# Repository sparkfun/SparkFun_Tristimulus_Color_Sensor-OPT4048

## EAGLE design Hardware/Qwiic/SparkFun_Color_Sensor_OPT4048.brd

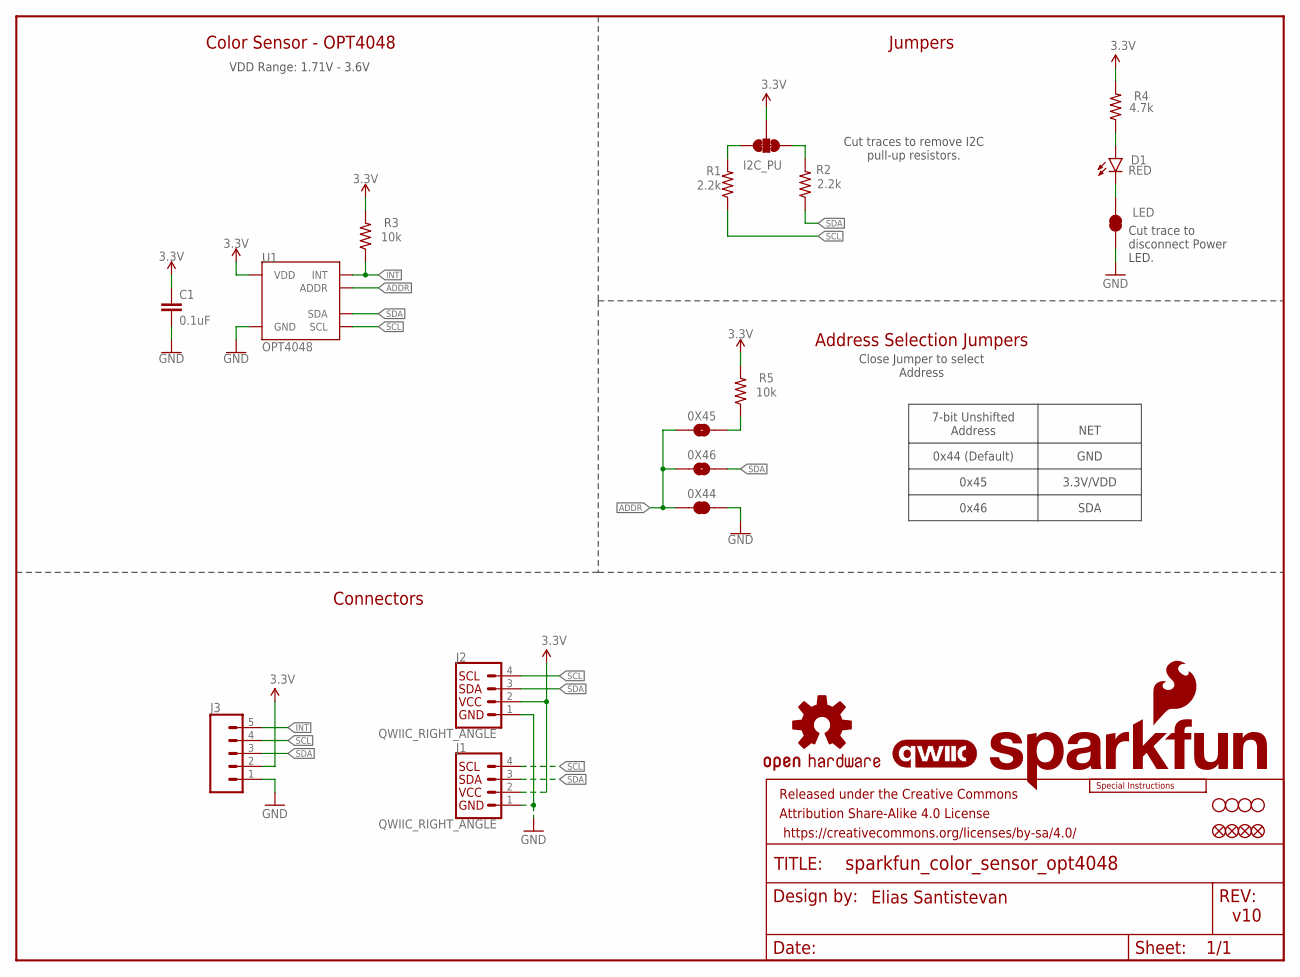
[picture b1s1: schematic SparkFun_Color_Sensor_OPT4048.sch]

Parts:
0X44: JUMPER-SMT_2_NC_TRACE_SILK; SMT-JUMPER_2_NC_TRACE_SILK
0X45, 0X46: JUMPER-SMT_2_NO_SILK; SMT-JUMPER_2_NO_SILK
C1: 0.1uF; 0402-TIGHT
D1: RED; LED-0603
FD1, FD2: FIDUCIALUFIDUCIAL; FIDUCIAL-MICRO
FID1, FID2: FIDUCIALUFIDUCIAL; FIDUCIAL-MICRO
FRAME1: FRAME-LETTER; CREATIVE_COMMONS
I2C_PU: S_MODE; SMT-JUMPER_3_2-NC_TRACE_SILK
J1, J2: QWIIC_RIGHT_ANGLE; JST04_1MM_RA
J3: CONN_05NO_SILK; 1X05_NO_SILK
LED: JUMPER-SMT_2_NC_TRACE_SILK; SMT-JUMPER_2_NC_TRACE_SILK
LOGO1: QWIIC_LOGO_4MM; QWIIC_4MM
LOGO2: OSHW-LOGOMINI; OSHW-LOGO-MINI
LOGO3: SFE_LOGO_NAME_FLAME.1_INCH; SFE_LOGO_NAME_FLAME_.1
LOGO4: SPECIAL_INSTRUCTIONS-ORDERING; ORDERING_INSTRUCTIONS
R1, R2: 2.2k; 0603
R3, R5: 10k; 0603
R4: 4.7k; 0603
STANDOFF1, STANDOFF2, STANDOFF3, STANDOFF4: STAND-OFFTIGHT; STAND-OFF-TIGHT
U1: OPT4048; FCSOT

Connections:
3.3V: C1.1, I2C_PU.2, J1.2, J2.2, J3.2, R3.2, R4.2, R5.2, U1.P1 (VDD)
ADDR: 0X44.1, 0X45.1, 0X46.1, U1.P2 (ADDR)
GND: 0X44.2, C1.2, J1.1, J2.1, J3.1, LED.1, U1.P4 (GND)
INT: J3.5, R3.1, U1.P7 (INT)
unnamed: D1.A, R4.1
unnamed: D1.C, LED.2
unnamed: 0X45.2, R5.1
unnamed: I2C_PU.1, R1.2
unnamed: I2C_PU.3, R2.2
SCL: J1.4, J2.4, J3.4, R1.1, U1.P5 (SCL)
SDA: 0X46.2, J1.3, J2.3, J3.3, R2.1, U1.P8 (SDA)

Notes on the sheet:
Color Sensor - OPT4048
Cut traces to remove I2C pull-up resistors.
VDD Range: 1.71V - 3.6V
v10
Jumpers
Cut trace to disconnect Power LED.
Connectors
Elias Santistevan
7-bit Unshifted Address
0x44 (Default)
0x45
0x46
GND
3.3V/VDD
SDA
Address Selection Jumpers
NET
Close Jumper to select Address

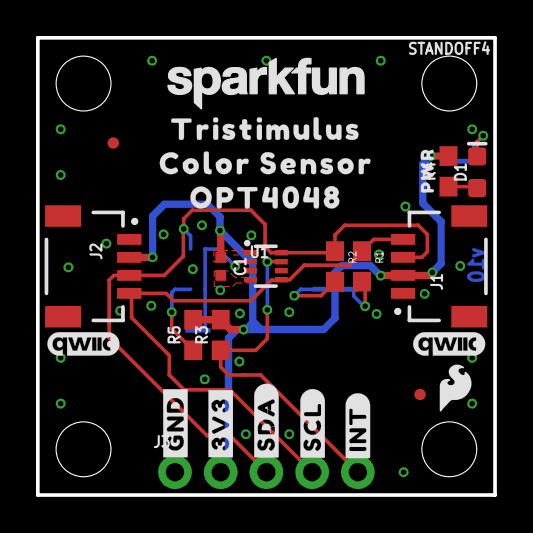
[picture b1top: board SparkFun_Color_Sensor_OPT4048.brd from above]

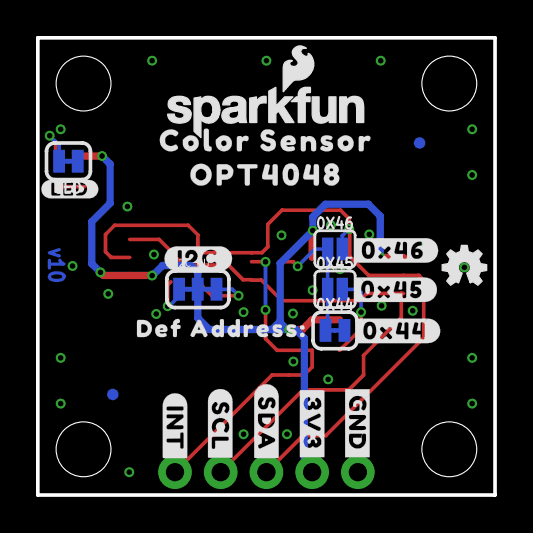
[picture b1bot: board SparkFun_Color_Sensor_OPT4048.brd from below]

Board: 2 copper layers, 25.4 x 25.4 mm, 54 parts (22 on the bottom side), 11 nets.

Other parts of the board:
LOGO5: QWIIC_LOGO_4MM; QWIIC_4MM
U$1, U$15: #3V3#1
U$2, U$17: #GND#0
U$3: #SDA#1
U$4: #SDA#4
U$5, U$22: #SCL#5
U$6: #INT#3
U$7: #INT#9
U$8: #0X44#18
U$9, U$12: COLOR_SENSOR227
U$10: #I2C#227
U$11: #0X45#18
U$13: TRISTIMULUS228
U$14, U$19: OPT4048229
U$16: #LED#11
U$18: SFE_LOGO_NAME_.1
U$20: DEF_ADDRESS#_17
U$21: #0X46#18
U$28: PWR8
U$29: SFE_LOGO_FLAME_.1

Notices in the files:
parts and their libraries:
SparkFun-Aesthetics: Licensing: Creative Commons ShareAlike 4.0 International - https://creativecommons.org/licenses/by-sa/4.0
SparkFun-Aesthetics: Released under the Creative Commons Attribution Share-Alike 4.0 License
SparkFun-Aesthetics: https://creativecommons.org/licenses/by-sa/4.0
